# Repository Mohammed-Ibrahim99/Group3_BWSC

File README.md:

# Group 3 - BridgeStone World Solar Car Race Challenge
All my development for the group project of Bridgestone World Solar Car race challenge in my 3rd Year. Group was awarded 2nd Place in a tradeshow event showcasing the project.

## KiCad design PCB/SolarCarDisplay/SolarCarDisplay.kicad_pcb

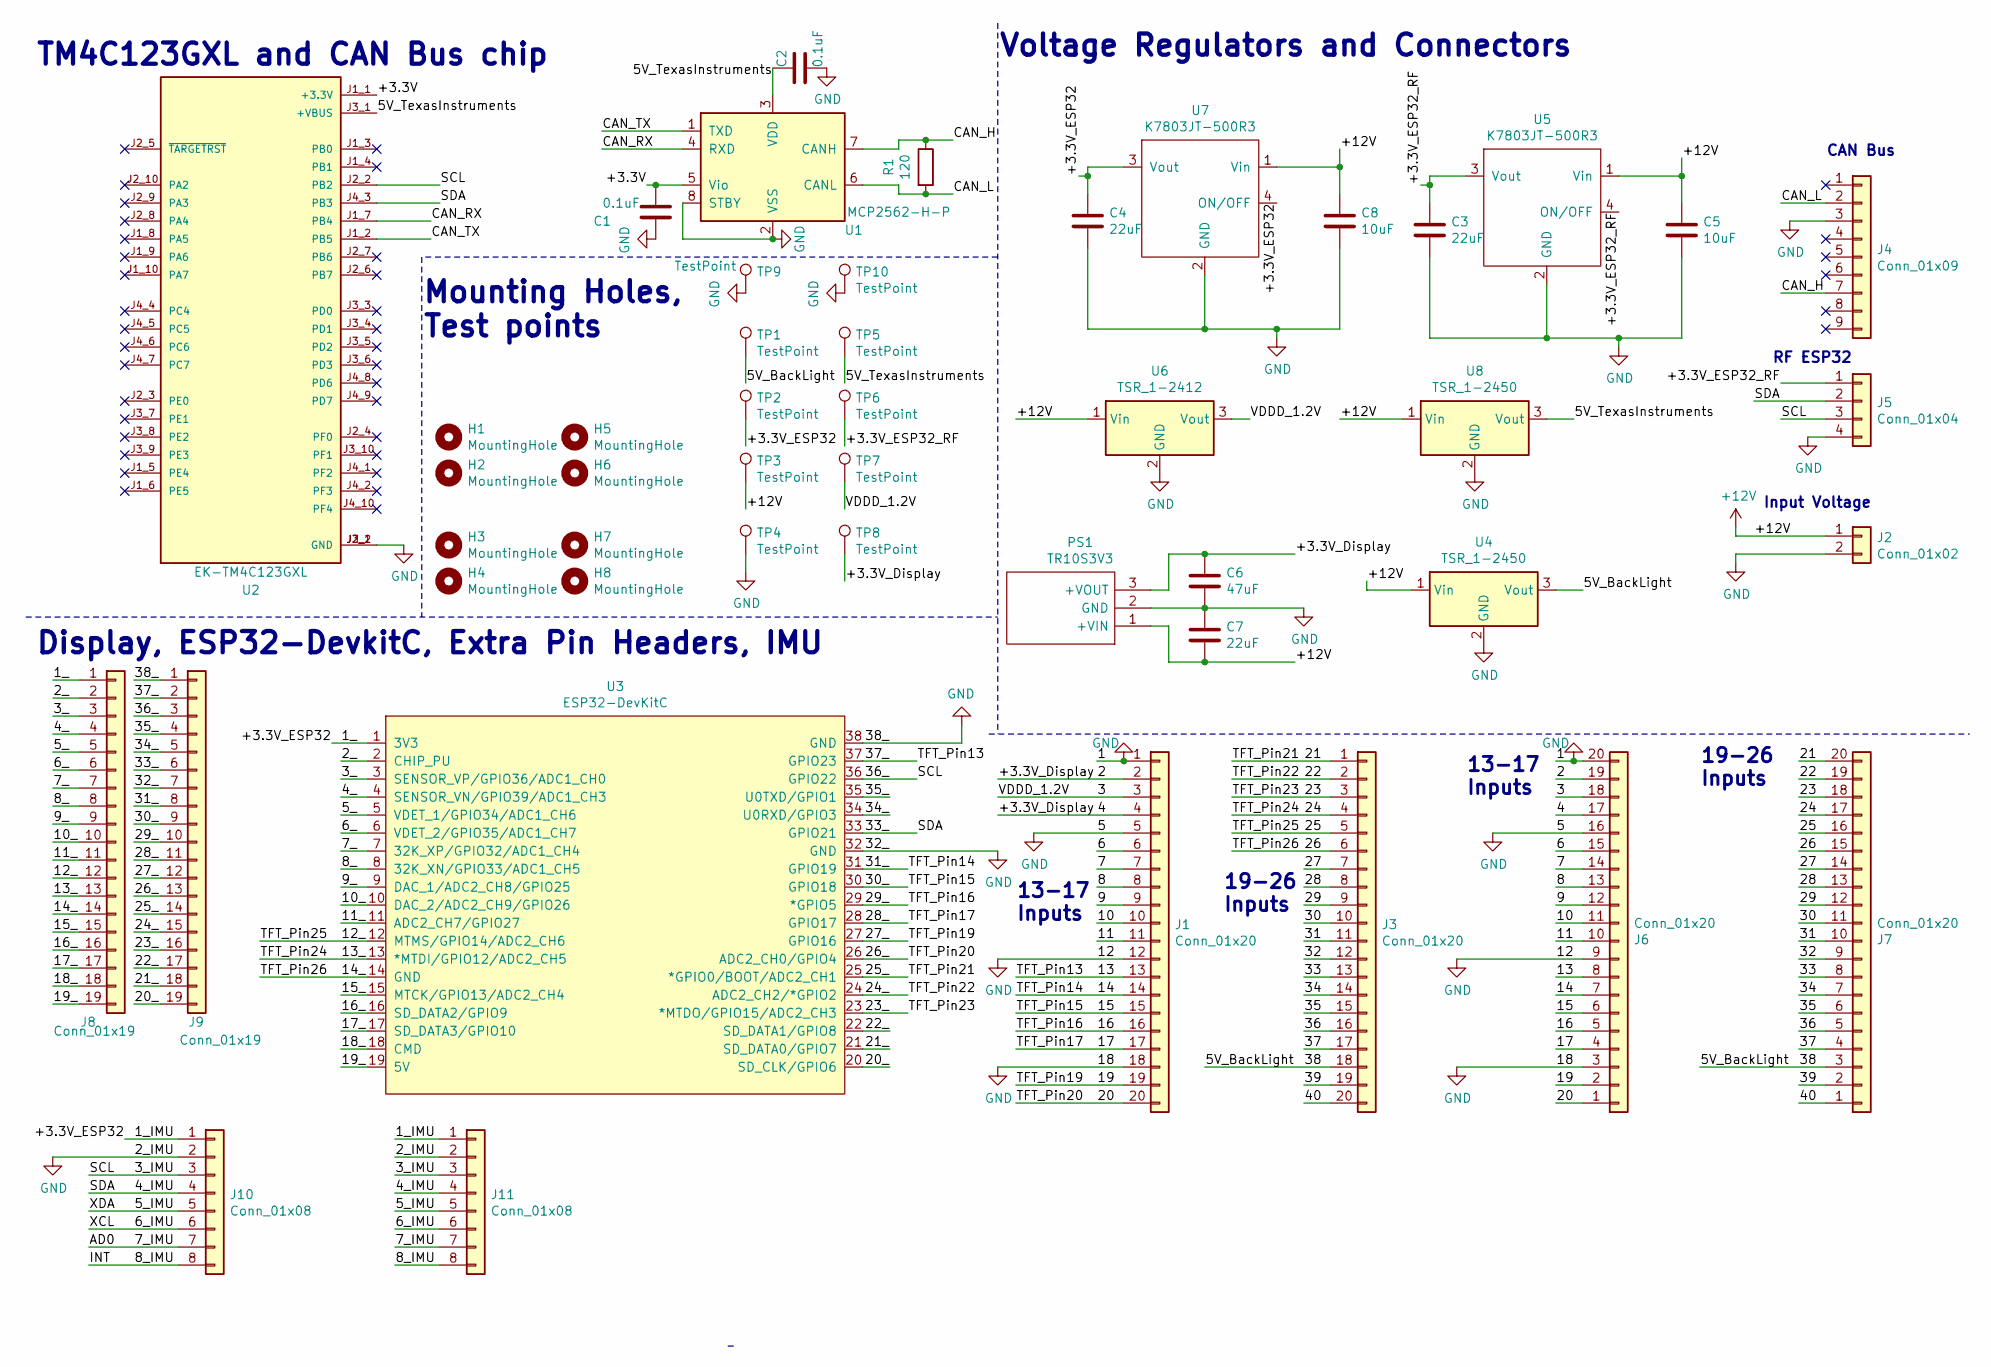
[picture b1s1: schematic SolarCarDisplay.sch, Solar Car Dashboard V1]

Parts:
C1, C2: 0.1uF; C_1206_3216Metric_Pad1.33x1.80mm_HandSolder
C3, C4, C7: 22uF; C_1206_3216Metric_Pad1.33x1.80mm_HandSolder
C5, C8: 10uF; C_1206_3216Metric_Pad1.33x1.80mm_HandSolder
C6: 47uF; C_1206_3216Metric_Pad1.33x1.80mm_HandSolder
H1, H2, H3, H4, H5, H6, H7, H8: MountingHole; MountingHole_2.5mm_Pad
J1, J3, J6, J7: Conn_01x20; PinSocket_1x20_P2.54mm_Vertical
J2: Conn_01x02; ATF132PBM03
J4: Conn_01x09; TE-5747840-6
J5: Conn_01x04; 347930040
J8, J9: Conn_01x19; PinHeader_1x19_P2.54mm_Vertical
J10, J11: Conn_01x08; PinHeader_1x08_P2.54mm_Vertical
PS1: TR10S3V3; TR05S3V3; Manufacturer_Part_Number TR10S3V3; Mouser Part Number 209-TR10S3V3
R1: 120; R_1206_3216Metric_Pad1.30x1.75mm_HandSolder
TP1, TP2, TP3, TP4, TP5, TP6, TP7, TP8, TP9, TP10: TestPoint; TestPoint_Plated_Hole_D2.0mm
U1: MCP2562-H-P; DIP-8_W7.62mm
U2: EK-TM4C123GXL; MODULE_EK-TM4C123GXL; PARTREV April 2013
U3: ESP32-DevKitC
U4, U8: TSR_1-2450; Converter_DCDC_TRACO_TSR-1_THT
U5, U7: K7803JT-500R3; CONV_K7803JT-500R3
U6: TSR_1-2412; Converter_DCDC_TRACO_TSR-1_THT

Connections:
+12V: C5.1, C7.2, C8.1, J2.1, PS1.1 (+VIN), TP3.1, U4.1 (Vin), U5.1 (Vin), U6.1 (Vin), U7.1 (Vin), U8.1 (Vin)
/2_: J8.2, U3.2 (CHIP_PU)
/3: J1.3, J6.18, TP7.1, U6.3 (Vout)
/3_: J8.3, U3.3 (SENSOR_VP/GPIO36/ADC1_CH0)
/4_: J8.4, U3.4 (SENSOR_VN/GPIO39/ADC1_CH3)
/5V_TexasInstruments: C2.1, TP5.1, U1.3 (VDD), U2.J3_1 (+VBUS), U8.3 (Vout)
/5_: J8.5, U3.5 (VDET_1/GPIO34/ADC1_CH6)
/5_IMU: J10.5, J11.5
/6: J1.6, J6.15
/6_: J8.6, U3.6 (VDET_2/GPIO35/ADC1_CH7)
/6_IMU: J10.6, J11.6
/7: J1.7, J6.14
/7_: J8.7, U3.7 (32K_XP/GPIO32/ADC1_CH4)
/7_IMU: J10.7, J11.7
/8: J1.8, J6.13
/8_: J8.8, U3.8 (32K_XN/GPIO33/ADC1_CH5)
/8_IMU: J10.8, J11.8
/9: J1.9, J6.12
/9_: J8.9, U3.9 (DAC_1/ADC2_CH8/GPIO25)
/10: J1.10, J6.11
/10_: J8.10, U3.10 (DAC_2/ADC2_CH9/GPIO26)
/11: J1.11, J6.10
/11_: J8.11, U3.11 (ADC2_CH7/GPIO27)
/12_: J3.5, J7.16, J8.12, U3.12 (MTMS/GPIO14/ADC2_CH6)
/13: J1.13, J6.8, J9.2, U3.37 (GPIO23)
/13_: J3.4, J7.17, J8.13, U3.13 (*MTDI/GPIO12/ADC2_CH5)
/14: J1.14, J6.7, J9.8, U3.31 (GPIO19)
/14_: J3.6, J7.15, J8.14, U3.14 (GND)
/15: J1.15, J6.6, J9.9, U3.30 (GPIO18)
/15_: J8.15, U3.15 (MTCK/GPIO13/ADC2_CH4)
/16: J1.16, J6.5, J9.10, U3.29 (*GPIO5)
/16_: J8.16, U3.16 (SD_DATA2/GPIO9)
/17: J1.17, J6.4, J9.11, U3.28 (GPIO17)
/17_: J8.17, U3.17 (SD_DATA3/GPIO10)
/18_: J8.18, U3.18 (CMD)
/19: J1.19, J6.2, J9.12, U3.27 (GPIO16)
/19_: J8.19, U3.19 (5V)
/20: J1.20, J6.1, J9.13, U3.26 (ADC2_CH0/GPIO4)
/20_: J9.19, U3.20 (SD_CLK/GPIO6)
/21: J3.1, J7.20, J9.14, U3.25 (*GPIO0/BOOT/ADC2_CH1)
/21_: J9.18, U3.21 (SD_DATA0/GPIO7)
/22: J3.2, J7.19, J9.15, U3.24 (ADC2_CH2/*GPIO2)
/22_: J9.17, U3.22 (SD_DATA1/GPIO8)
/23: J3.3, J7.18, J9.16, U3.23 (*MTDO/GPIO15/ADC2_CH3)
/27: J3.7, J7.14
/28: J3.8, J7.13
/29: J3.9, J7.12
/30: J3.10, J7.11
/31: J3.11, J7.10
/32: J3.12, J7.9
/33: J3.13, J7.8
/33_: J5.2, J9.6, J10.4, J11.4, U2.J4_3 (PB3), U3.33 (GPIO21)
/34: J3.14, J7.7
/34_: J9.5, U3.34 (U0RXD/GPIO3)
/35: J3.15, J7.6
/35_: J9.4, U3.35 (U0TXD/GPIO1)
/36: J3.16, J7.5
/36_: J5.3, J9.3, J10.3, J11.3, U2.J2_2 (PB2), U3.36 (GPIO22)
/37: J3.17, J7.4
/38: J3.18, J7.3, TP1.1, U4.3 (Vout)
/39: J3.19, J7.2
/40: J3.20, J7.1
/+3.3V: C1.1, U1.5 (Vio), U2.J1_1 (+3.3V)
/+3.3V_Display: C6.1, J1.2, J1.4, J6.17, J6.19, PS1.3 (+VOUT), TP8.1
/+3.3V_ESP32: C4.1, J8.1, J10.1, J11.1, TP2.1, U3.1 (3V3), U7.3 (Vout), U7.4 (ON/OFF)
/+3.3V_ESP32_RF: C3.1, J5.1, TP6.1, U5.3 (Vout), U5.4 (ON/OFF)
/CAN_H: J4.7, R1.1, U1.7 (CANH)
/CAN_L: J4.2, R1.2, U1.6 (CANL)
/CAN_RX: U1.4 (RXD), U2.J1_7 (PB4)
/CAN_TX: U1.1 (TXD), U2.J1_2 (PB5)
GND: C1.2, C2.2, C3.2, C4.2, C5.2, C6.2, C7.1, C8.2, J1.1, J1.5, J1.12, J1.18, J2.2, J4.3, J5.4, J6.3, J6.9, J6.16, J6.20, J9.1, J9.7, J10.2, J11.2, PS1.2 (GND), TP4.1, TP9.1, TP10.1, U1.2 (VSS), U1.8 (STBY), U2.J2_1 (GND), U2.J3_2 (GND), U3.32 (GND), U3.38 (GND), U4.2 (GND), U5.2 (GND), U6.2 (GND), U7.2 (GND), U8.2 (GND)

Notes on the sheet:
Voltage Regulators and Connectors
13-17 Inputs
19-26 Inputs
CAN Bus
RF ESP32
Input Voltage
Display, ESP32-DevkitC, Extra Pin Headers, IMU
TM4C123GXL and CAN Bus chip
Mounting Holes, Test points

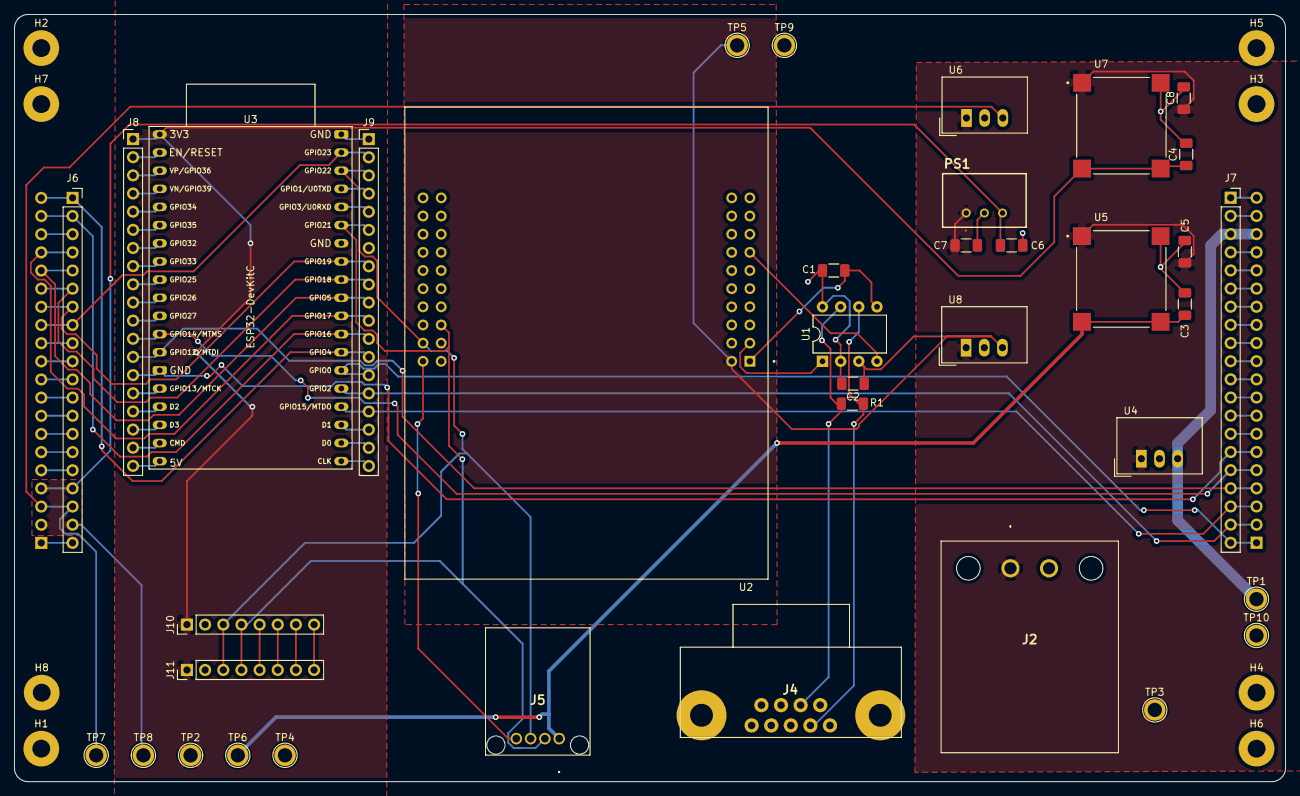
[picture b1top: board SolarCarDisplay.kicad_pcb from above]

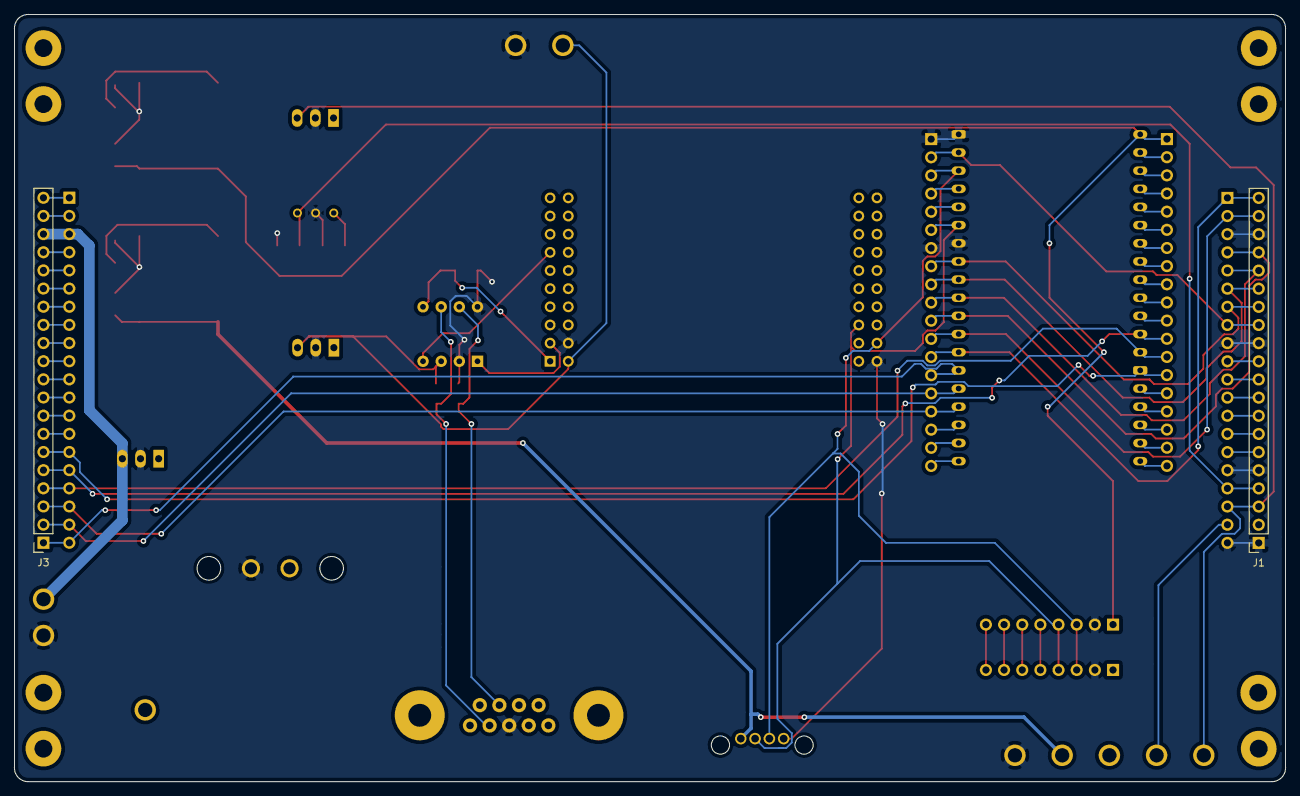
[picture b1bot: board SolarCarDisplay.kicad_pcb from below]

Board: 2 copper layers, 177.8 x 107.3 mm, 47 parts (2 on the bottom side), 71 nets.

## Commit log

2023-03-20 PCB files added
2023-03-20 Added all arduino files
2023-03-20 Added MATLAB files
